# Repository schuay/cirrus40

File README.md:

# Cirrus40 Keyboard

The Cirrus40 is a 40% split mechanical keyboard, with an ortholinear layout and a focus on usable rotary encoders.

## Design Considerations

- A **3x thumb cluster** where each key is equally usable and comfortable to reach.
- **Rotary encoders** under the palms are nicely reachable without moving hands from the homerow position. One-handed use together with homerow modifiers (think: switching tabs, workspaces; word-by-word navigation, selection, and deletion). Hardware debouncing for the perfect input signal; no more missed transitions.
- A **full 3d printed case** protects the internals.
- An **optional 3d printed 30deg tenting stand** for rock-solid tenting. The tenting stand integrates perfectly with the case.
- An **ortholinear** layout. Why not columnar stagger: it's comfortable at rest, but increases separation between the pinky and ring fingers in motion.
- A **hot-pluggable wired USB-C interconnect** between halves. USB-C cables are widely available.
- Support for **both wired and wireless** operation.
- Simple tenting using M3 screws.
- No toys: no LEDs, no displays.
- Only widely available and inexpensive parts.

The Cirrus40 combines some of the favorite aspects of my previous builds (the Cheapino's thumb cluster and the Lotus58's key layout and USB-C interconnect). I got a bit fixated on optimizing encoder precision and ergonomics, which is why you'll see the hardware debouncing circuit, the below-palm position, and the strong recommendation for quality Alps encoders.

## Firmware

**QMK**: [qmk_firmware](https://github.com/schuay/qmk_firmware/tree/add_cirrus40). My own keymap is available as an example at [qmk_userspace](https://github.com/schuay/qmk_userspace).

**ZMK**: Contributions welcome. [zmk-config](https://github.com/schuay/zmk-config) hasn't been updated for Cirrus40 Revision 2 yet.

## Required Files

All files required for manufacture are located in the most recent release directory.

- **[PCB Gerber Files](releases/20251220/pcb-gerber.zip)**: For manufacturing the printed circuit boards.
- **[3D Case/Stand Files](releases/20251220/case-steps.tar.xz)**: STEP files for printing the case and optional tenting stand.

## Ordering guide

TLDR: PCB and case manufacturing from JLCPCB, electronics components from LCSC, and the rest from AliExpress with Choice shipping.

- [jlcpcb.com](jlcpcb.com):
  - For the PCB: it's safe to stick with default values. 
  - For the case: I used 9600 Resin (Spray Painting-Matte-Black) for the case and PA12-HP Nylon for the tenting stand with good results. Please let me know if you experiment with other materials.
- [lcsc.com](lcsc.com): See [doc/bom.csv](doc/bom.csv) for more info. Note that the [USB-C connector I used](https://www.lcsc.com/product-detail/C963373.html) is currently out of stock and NOT included in [doc/bom.csv](doc/bom.csv).
- [aliexpress.com](aliexpress.com): Great for switches, keycaps, encoder heads, the RP2040 ProMicro MCU, MCU pin headers, screws, spacers, nuts, etc. I've had good experiences with "Choice" shipping.

Note: jlcpcb.com and lcsc.com offer combined shipping; this is not recommended, as it was more complex, more expensive, and slower when I tried it.

## Build guide

A detailed, step-by-step build guide is not yet available. Contributions on this front are very welcome!

However, the build process is straightforward for those with some experience in hand-soldering keyboards. The soldering difficulty is medium-to-easy; the surface-mount components are in a large (0805) package and are suitable for hand-soldering. The USB-C connector is also simpler than it looks: the wiring is such that all data pins can simply be bridged together (i.e. precise drag-soldering is not strictly needed).

I usually do the USB-C connector and SMD components first, followed by diodes and hotswap sockets; and finally the MCU plus socket and encoders. All components (except the encoder) go on the bottom side of the PCB. Consult the kicad files if something is unclear. A multimeter is good to have around for verification and error search.

## Bill of Materials

A single keyboard build costs around 80EUR including shipping and customs from JLCPCB and LCSC.

**Core Components**
| Part | Quantity | Notes |
| --- | --- | --- |
| Reversible PCB | 2 | From the Gerber files |
| 3D Printed Case | 1 | From the STEP files. Tenting stand is optional. |
| MX switches | 36 | |
| MX hotswap sockets | 36 | |
| EC11 rotary encoders | 2 | **ALPS EC11E15244G1** is strongly recommended. |
| Encoder knobs | 2 | |
| 1N4148 or 1N4148W diodes | 40 | SOD-123 or SOD-323 package |
| 100nF capacitors | 4 | 0805 package |
| 10kOhm resistors | 4 | 0805 package |
| 8.2kOhm resistors | 4 | 0805 package |
| MCU Sockets / Pin Headers | 2 sets | For socketing the microcontrollers |

**Wired Build Components**
| Part | Quantity | Notes |
| --- | --- | --- |
| Pro Micro (RP2040) MCU | 2 | |
| Ferrite beads | 4 | 0805 package, e.g., 220Ω@100MHz |
| USB-C mid-mount connector | 2 | e.g., LCSC C963373 |
| ESD protection diode | 2 | e.g., LCSC C558418 |

**Wireless Build Components**
| Part | Quantity | Notes |
| --- | --- | --- |
| nice!nano v2 MCU | 2 | |
| LiPo Battery | 2 | 301230 (110 mAh) size recommended |
| Power slide switch | 2 | e.g., LCSC C431540 |

**Hardware**
| Part | Quantity | Notes |
| --- | --- | --- |
| M2x4mm screws | 20 | Use M2x6mm for the 4 case holes if using the tenting stand |
| M2x7mm spacers | 10 | |
| M3 screws and nuts | 4 (opt) | For basic, non-stand tenting |

## Release history

Released files can be found in the releases/ directory.

- [releases/20251220](releases/20251220): Revision 2. 3x5+3 with a full 3d printed case and 30deg tenting stand. Hardware encoder debouncing.
- [releases/20251001](releases/20251001): Revision 1. 3x6+3 with a sandwich case.

## Revision 1 Gallery

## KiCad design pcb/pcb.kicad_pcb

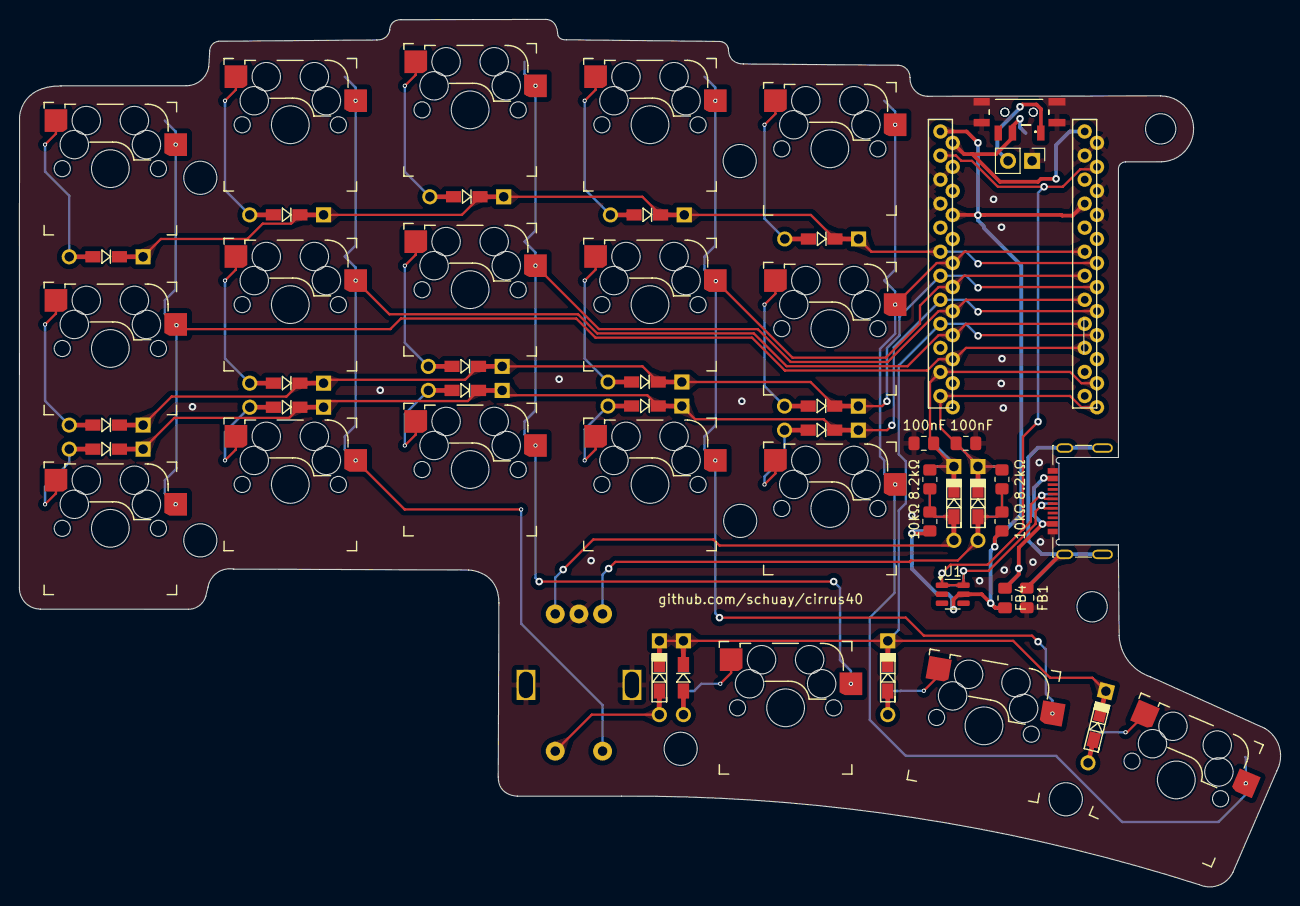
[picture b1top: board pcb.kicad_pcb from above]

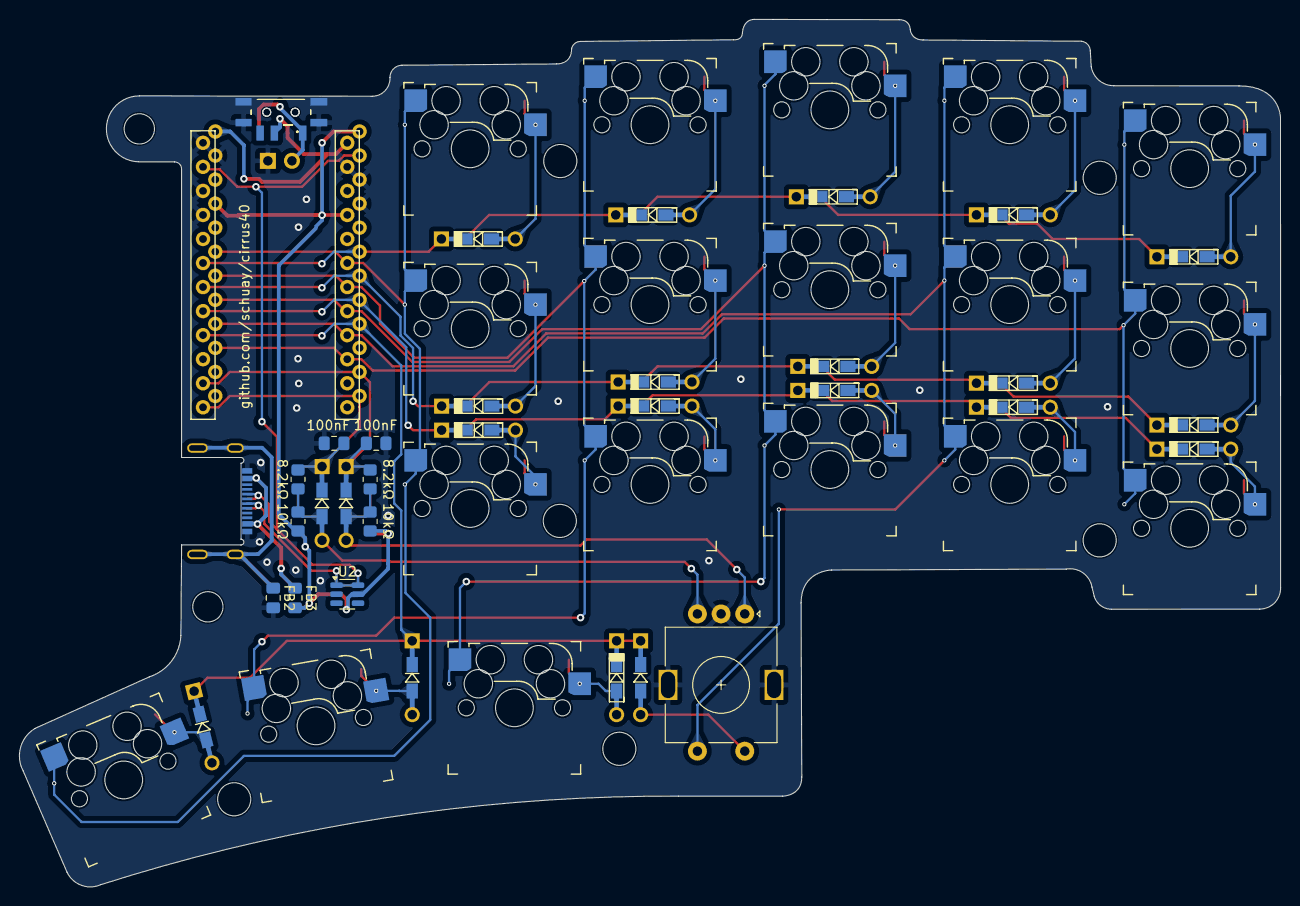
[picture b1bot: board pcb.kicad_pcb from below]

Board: 2 copper layers, 133.2 x 91.6 mm, 63 parts (45 on the bottom side), 39 nets.

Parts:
8.2kΩ, 8.2kΩ#2, 8.2kΩ#3, 8.2kΩ#4: 8kOhm; R_0805_2012Metric_Pad1.20x1.40mm_HandSolder
10kΩ, 10kΩ#2, 10kΩ#3, 10kΩ#4: 10kOhm; R_0805_2012Metric_Pad1.20x1.40mm_HandSolder
100nF, 100nF#2, 100nF#3, 100nF#4: 470nF; C_0805_2012Metric_Pad1.18x1.45mm_HandSolder
D1, D2, D3, D4, D5, D6, D7, D8, D9, D10, D11, D12, D13, D14, D15, D16, D17, D18, D19, D20, D21: DIODE; Diode-dual
ENC1: RotaryEncoder_Switch_MP; RotaryEncoder_Alps_EC11E-Switch_Vertical_H20mm
FB1, FB2, FB3, FB4: Ferrite Bead; C_0805_2012Metric_Pad1.18x1.45mm_HandSolder
J1: USB_C_Receptacle_USB2.0_16P; Molex-216990_GCT-USB45xx_HRO-TYPE-C-31-M-13x-PiMicro_1_DOUB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
J2: Conn_01x02; PinHeader_1x02_P2.54mm_Vertical
K1, K2, K3, K4, K5, K6, K7, K8, K9, K10, K11, K12, K13, K14, K15, K16, K17, K18: SW_Push; SW_MX_HotSwap_Reversible
S1, S2: MSK12C02
U1, U2: SRV05-4; SOT-23-6
U3: ProMicro; ProMicro_Reversible_orig

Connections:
/Batt: J2.2, S1.NC, S2.NC
/VCC_LINK: FB3.1, FB4.1, J1.A4 (VBUS), J1.A9 (VBUS), J1.B4 (VBUS), J1.B9 (VBUS)
Battery: S1.COM, S2.COM, U3.5V
COL0: K15.1, K16.1, K17.1, K18.1, U3.28 (GP28)
COL1: K11.1, K12.1, K13.1, K14.1, U3.27 (GP27)
COL2: K7.1, K8.1, K9.1, K10.1, U3.26 (GP26)
COL3: ENC1.S1, K4.1, K5.1, K6.1, U3.22 (GP22)
COL4: K1.1, K2.1, K3.1, U3.20 (GP20)
DATA: J1.A7 (D-), J1.B7 (D-), U1.1 (IO1), U1.6 (IO4), U2.1 (IO1), U2.6 (IO4), U3.1 (GP1)
ENCA: 8.2kΩ#2.1, 8.2kΩ#3.1, 10kΩ#2.2, 10kΩ#4.2, D12.1 (K), ENC1.A
ENCA_DB: 8.2kΩ#2.2, 8.2kΩ#3.2, 100nF#2.1, 100nF#3.1, D12.2 (A), U3.8 (GP8)
ENCB: 8.2kΩ.1, 8.2kΩ#4.1, 10kΩ.2, 10kΩ#3.2, D21.1 (K), ENC1.B
ENCB_DB: 8.2kΩ.2, 8.2kΩ#4.2, 100nF.1, 100nF#4.1, D21.2 (A), U3.9 (GP9)
GND: 100nF.2, 100nF#2.2, 100nF#3.2, 100nF#4.2, ENC1.C, ENC1.MP, FB1.2, FB2.2, J1.A1 (GND), J1.A12 (GND), J1.B1 (GND), J1.B12 (GND), J2.1, S1.MP (GND), S2.MP (GND), U1.2 (VN), U2.2 (VN), U3.0 (GP0), U3.GND
unnamed: D1.1 (K), K1.2
unnamed: D2.1 (K), K2.2
unnamed: D3.1 (K), K3.2
unnamed: D4.1 (K), K4.2
unnamed: D5.1 (K), K5.2
unnamed: D6.1 (K), K6.2
unnamed: D7.1 (K), ENC1.S2
unnamed: D8.1 (K), K7.2
unnamed: D9.1 (K), K8.2
unnamed: D10.1 (K), K9.2
unnamed: D11.1 (K), K10.2
unnamed: D13.1 (K), K11.2
unnamed: D14.1 (K), K12.2
unnamed: D15.1 (K), K13.2
unnamed: D16.1 (K), K14.2
unnamed: D17.1 (K), K15.2
unnamed: D18.1 (K), K16.2
unnamed: D19.1 (K), K17.2
unnamed: D20.1 (K), K18.2
unnamed: FB1.1, FB2.1, J1.S1 (SHIELD)
ROW0: D1.2 (A), D4.2 (A), D8.2 (A), D13.2 (A), D17.2 (A), U3.3 (GP3)
ROW1: D2.2 (A), D5.2 (A), D9.2 (A), D14.2 (A), D18.2 (A), U3.4 (GP4)
ROW2: D3.2 (A), D6.2 (A), D10.2 (A), D15.2 (A), D19.2 (A), U3.5 (GP5)
ROW3: D7.2 (A), D11.2 (A), D16.2 (A), D20.2 (A), U3.6 (GP6)
VCC: 10kΩ.1, 10kΩ#2.1, 10kΩ#3.1, 10kΩ#4.1, FB3.2, FB4.2, U1.5 (VP), U2.5 (VP), U3.3V3, U3.99 (GP0L)

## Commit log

2025-10-01 add a pcb render
2025-10-01 add photos
2025-11-02 cirrus40, second manufactured version
2025-11-06 add case files
2025-12-20 add cap/resistor labels and github link
2025-12-20 update for revision 2
2026-06-07 addtl photos
2026-06-07 extend documentation
